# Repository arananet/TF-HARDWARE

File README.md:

# TF-HARDWARE
A backup (04-04-2017) of the last TF repo that includes the projects (TF520,TF530,A3640 & breakout). All the work belongs to Stephen Leary, I just share the files as a repo backup.

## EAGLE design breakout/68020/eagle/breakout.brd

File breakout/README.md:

Terrible Fire Break Out Boards
=================================

* 68020 - PGA114 Breakout

You may get any PCB manufacturer to produce the board for you. The board is 2-layer. I recommend these dirtypcbs links...

http://dirtypcbs.com/view.php?share=26129&accesskey=53f7f219ee0d339a3d1a7b1910aeaeed

* 68030 - PGA128 Breakout

You may get any PCB manufacturer to produce the board for you. The board is 2-layer. I recommend these dirtypcbs links...

http://dirtypcbs.com/view.php?share=28380&accesskey=9c851266aeee43fccca2846767b09b1c

* CD32 - MCA-182 Breakout

Work in Progress

* Libraries

The terriblefire.lbr file contains the following parts :-

XC9572XL-VQ64 (unverfied)

XC95144XL-TQ100 (unverified)

MC68SEC000-QFP64 (unverfied)

These parts are free to use but come with absolutely NO WARRANTY and in many cases have not been verified. 

* Tools

The following GPL tools are available.

54600.py - (Captures the output of a 56400 series scope and writes the output to a VCD file).

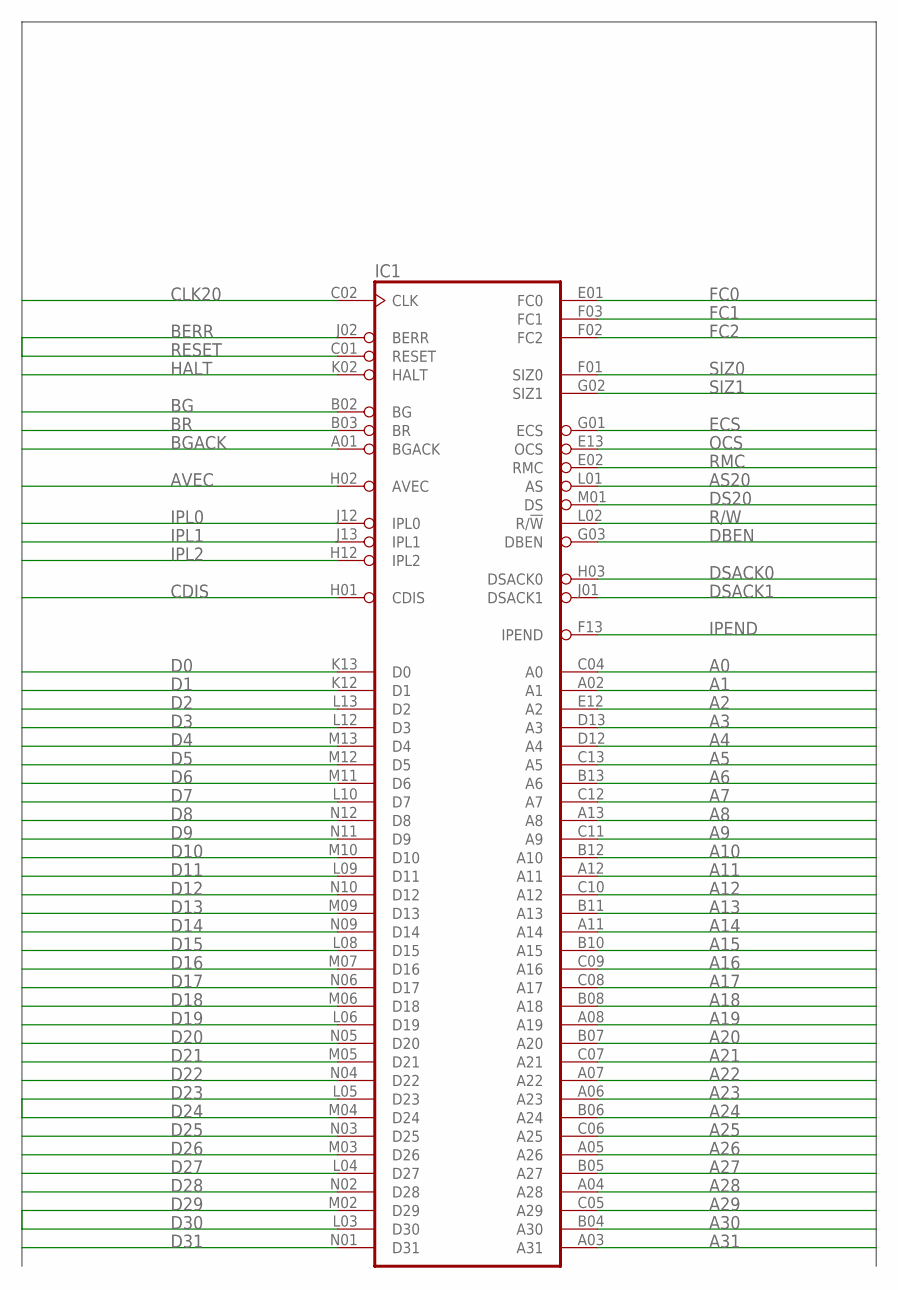
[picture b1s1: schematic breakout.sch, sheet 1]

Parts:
IC1: MC68020RC; MPGA114

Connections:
A0: IC1.C04 (A0); also elsewhere on the board
A1: IC1.A02 (A1); also elsewhere on the board
A2: IC1.E12 (A2); also elsewhere on the board
A3: IC1.D13 (A3); also elsewhere on the board
A4: IC1.D12 (A4); also elsewhere on the board
A5: IC1.C13 (A5); also elsewhere on the board
A6: IC1.B13 (A6); also elsewhere on the board
A7: IC1.C12 (A7); also elsewhere on the board
A8: IC1.A13 (A8); also elsewhere on the board
A9: IC1.C11 (A9); also elsewhere on the board
A10: IC1.B12 (A10); also elsewhere on the board
A11: IC1.A12 (A11); also elsewhere on the board
A12: IC1.C10 (A12); also elsewhere on the board
A13: IC1.B11 (A13); also elsewhere on the board
A14: IC1.A11 (A14); also elsewhere on the board
A15: IC1.B10 (A15); also elsewhere on the board
A16: IC1.C09 (A16); also elsewhere on the board
A17: IC1.C08 (A17); also elsewhere on the board
A18: IC1.B08 (A18); also elsewhere on the board
A19: IC1.A08 (A19); also elsewhere on the board
A20: IC1.B07 (A20); also elsewhere on the board
A21: IC1.C07 (A21); also elsewhere on the board
A22: IC1.A07 (A22); also elsewhere on the board
A23: IC1.A06 (A23); also elsewhere on the board
A24: IC1.B06 (A24); also elsewhere on the board
A25: IC1.C06 (A25); also elsewhere on the board
A26: IC1.A05 (A26); also elsewhere on the board
A27: IC1.B05 (A27); also elsewhere on the board
A28: IC1.A04 (A28); also elsewhere on the board
A29: IC1.C05 (A29); also elsewhere on the board
A30: IC1.B04 (A30); also elsewhere on the board
A31: IC1.A03 (A31); also elsewhere on the board
AS20: IC1.L01 (AS); also elsewhere on the board
AVEC: IC1.H02 (AVEC); also elsewhere on the board
BERR: IC1.J02 (BERR); also elsewhere on the board
BG: IC1.B02 (BG)
BGACK: IC1.A01 (BGACK); also elsewhere on the board
BR: IC1.B03 (BR); also elsewhere on the board
CDIS: IC1.H01 (CDIS); also elsewhere on the board
CLK20: IC1.C02 (CLK); also elsewhere on the board
D0: IC1.K13 (D0); also elsewhere on the board
D1: IC1.K12 (D1); also elsewhere on the board
D2: IC1.L13 (D2); also elsewhere on the board
D3: IC1.L12 (D3); also elsewhere on the board
D4: IC1.M13 (D4); also elsewhere on the board
D5: IC1.M12 (D5); also elsewhere on the board
D6: IC1.M11 (D6); also elsewhere on the board
D7: IC1.L10 (D7); also elsewhere on the board
D8: IC1.N12 (D8); also elsewhere on the board
D9: IC1.N11 (D9); also elsewhere on the board
D10: IC1.M10 (D10); also elsewhere on the board
D11: IC1.L09 (D11); also elsewhere on the board
D12: IC1.N10 (D12); also elsewhere on the board
D13: IC1.M09 (D13); also elsewhere on the board
D14: IC1.N09 (D14); also elsewhere on the board
D15: IC1.L08 (D15); also elsewhere on the board
D16: IC1.M07 (D16); also elsewhere on the board
D17: IC1.N06 (D17); also elsewhere on the board
D18: IC1.M06 (D18); also elsewhere on the board
D19: IC1.L06 (D19); also elsewhere on the board
D20: IC1.N05 (D20); also elsewhere on the board
D21: IC1.M05 (D21); also elsewhere on the board
D22: IC1.N04 (D22); also elsewhere on the board
D23: IC1.L05 (D23); also elsewhere on the board
D24: IC1.M04 (D24); also elsewhere on the board
D25: IC1.N03 (D25); also elsewhere on the board
D26: IC1.M03 (D26); also elsewhere on the board
D27: IC1.L04 (D27); also elsewhere on the board
D28: IC1.N02 (D28); also elsewhere on the board
D29: IC1.M02 (D29); also elsewhere on the board
D30: IC1.L03 (D30); also elsewhere on the board
D31: IC1.N01 (D31); also elsewhere on the board
DBEN: IC1.G03 (DBEN); also elsewhere on the board
DS20: IC1.M01 (DS); also elsewhere on the board
DSACK0: IC1.H03 (DSACK0); also elsewhere on the board
DSACK1: IC1.J01 (DSACK1); also elsewhere on the board
ECS: IC1.G01 (ECS); also elsewhere on the board
FC0: IC1.E01 (FC0); also elsewhere on the board
FC1: IC1.F03 (FC1); also elsewhere on the board
FC2: IC1.F02 (FC2); also elsewhere on the board
GND: IC1.A10 (GND), IC1.B01 (GND), IC1.B09 (GND), IC1.C03 (GND), IC1.F12 (GND), IC1.G12 (GND), IC1.H13 (GND), IC1.J03 (GND), IC1.K01 (GND), IC1.K03 (GND), IC1.L07 (GND), IC1.L11 (GND), IC1.N07 (GND); also elsewhere on the board
HALT: IC1.K02 (HALT); also elsewhere on the board
IPEND: IC1.F13 (IPEND); also elsewhere on the board
IPL0: IC1.J12 (IPL0); also elsewhere on the board
IPL1: IC1.J13 (IPL1); also elsewhere on the board
IPL2: IC1.H12 (IPL2); also elsewhere on the board
OCS: IC1.E13 (OCS); also elsewhere on the board
R/W: IC1.L02 (R/!W); also elsewhere on the board
RESET: IC1.C01 (RESET); also elsewhere on the board
RMC: IC1.E02 (RMC); also elsewhere on the board
SIZ0: IC1.F01 (SIZ0); also elsewhere on the board
SIZ1: IC1.G02 (SIZ1); also elsewhere on the board
VCC: IC1.A09 (VCC), IC1.D01 (VCC), IC1.D02 (VCC), IC1.D03 (VCC), IC1.E03 (VCC), IC1.G11 (VCC), IC1.G13 (VCC), IC1.M08 (VCC), IC1.N08 (VCC), IC1.N13 (VCC); also elsewhere on the board

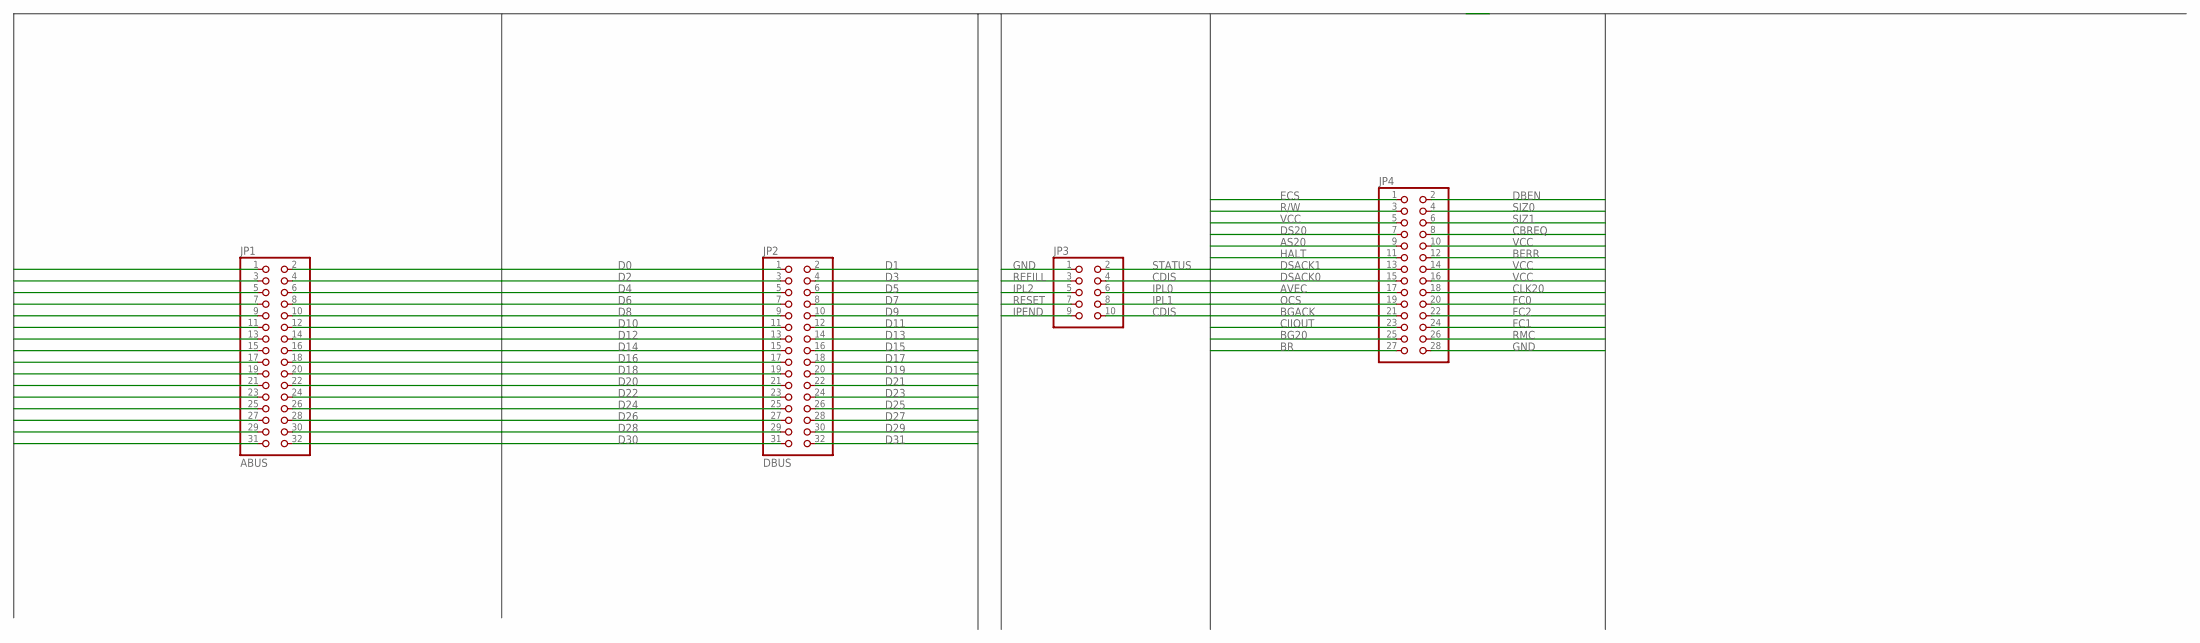
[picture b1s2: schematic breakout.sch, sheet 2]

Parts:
JP1: ABUS; 2X16
JP2: DBUS; 2X16
JP3: PINHD-2X5; 2X05
JP4: PINHD-2X14; 2X14

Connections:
A0: JP1.1; also elsewhere on the board
A1: JP1.2; also elsewhere on the board
A2: JP1.3; also elsewhere on the board
A3: JP1.4; also elsewhere on the board
A4: JP1.5; also elsewhere on the board
A5: JP1.6; also elsewhere on the board
A6: JP1.7; also elsewhere on the board
A7: JP1.8; also elsewhere on the board
A8: JP1.9; also elsewhere on the board
A9: JP1.10; also elsewhere on the board
A10: JP1.11; also elsewhere on the board
A11: JP1.12; also elsewhere on the board
A12: JP1.13; also elsewhere on the board
A13: JP1.14; also elsewhere on the board
A14: JP1.15; also elsewhere on the board
A15: JP1.16; also elsewhere on the board
A16: JP1.17; also elsewhere on the board
A17: JP1.18; also elsewhere on the board
A18: JP1.19; also elsewhere on the board
A19: JP1.20; also elsewhere on the board
A20: JP1.21; also elsewhere on the board
A21: JP1.22; also elsewhere on the board
A22: JP1.23; also elsewhere on the board
A23: JP1.24; also elsewhere on the board
A24: JP1.25; also elsewhere on the board
A25: JP1.26; also elsewhere on the board
A26: JP1.27; also elsewhere on the board
A27: JP1.28; also elsewhere on the board
A28: JP1.29; also elsewhere on the board
A29: JP1.30; also elsewhere on the board
A30: JP1.31; also elsewhere on the board
A31: JP1.32; also elsewhere on the board
AS20: JP4.9; also elsewhere on the board
AVEC: JP4.17; also elsewhere on the board
BERR: JP4.12; also elsewhere on the board
BG20: JP4.25
BGACK: JP4.21; also elsewhere on the board
BR: JP4.27; also elsewhere on the board
CBREQ: JP4.8
CDIS: JP3.4, JP3.10; also elsewhere on the board
CIIOUT: JP4.23
CLK20: JP4.18; also elsewhere on the board
D0: JP2.1; also elsewhere on the board
D1: JP2.2; also elsewhere on the board
D2: JP2.3; also elsewhere on the board
D3: JP2.4; also elsewhere on the board
D4: JP2.5; also elsewhere on the board
D5: JP2.6; also elsewhere on the board
D6: JP2.7; also elsewhere on the board
D7: JP2.8; also elsewhere on the board
D8: JP2.9; also elsewhere on the board
D9: JP2.10; also elsewhere on the board
D10: JP2.11; also elsewhere on the board
D11: JP2.12; also elsewhere on the board
D12: JP2.13; also elsewhere on the board
D13: JP2.14; also elsewhere on the board
D14: JP2.15; also elsewhere on the board
D15: JP2.16; also elsewhere on the board
D16: JP2.17; also elsewhere on the board
D17: JP2.18; also elsewhere on the board
D18: JP2.19; also elsewhere on the board
D19: JP2.20; also elsewhere on the board
D20: JP2.21; also elsewhere on the board
D21: JP2.22; also elsewhere on the board
D22: JP2.23; also elsewhere on the board
D23: JP2.24; also elsewhere on the board
D24: JP2.25; also elsewhere on the board
D25: JP2.26; also elsewhere on the board
D26: JP2.27; also elsewhere on the board
D27: JP2.28; also elsewhere on the board
D28: JP2.29; also elsewhere on the board
D29: JP2.30; also elsewhere on the board
D30: JP2.31; also elsewhere on the board
D31: JP2.32; also elsewhere on the board
DBEN: JP4.2; also elsewhere on the board
DS20: JP4.7; also elsewhere on the board
DSACK0: JP4.15; also elsewhere on the board
DSACK1: JP4.13; also elsewhere on the board
ECS: JP4.1; also elsewhere on the board
FC0: JP4.20; also elsewhere on the board
FC1: JP4.24; also elsewhere on the board
FC2: JP4.22; also elsewhere on the board
GND: JP3.1, JP4.28; also elsewhere on the board
HALT: JP4.11; also elsewhere on the board
IPEND: JP3.9; also elsewhere on the board
IPL0: JP3.6; also elsewhere on the board
IPL1: JP3.8; also elsewhere on the board
IPL2: JP3.5; also elsewhere on the board
OCS: JP4.19; also elsewhere on the board
R/W: JP4.3; also elsewhere on the board
REFILL: JP3.3
RESET: JP3.7; also elsewhere on the board
RMC: JP4.26; also elsewhere on the board
SIZ0: JP4.4; also elsewhere on the board
SIZ1: JP4.6; also elsewhere on the board
STATUS: JP3.2
VCC: JP4.5, JP4.10, JP4.14, JP4.16; also elsewhere on the board

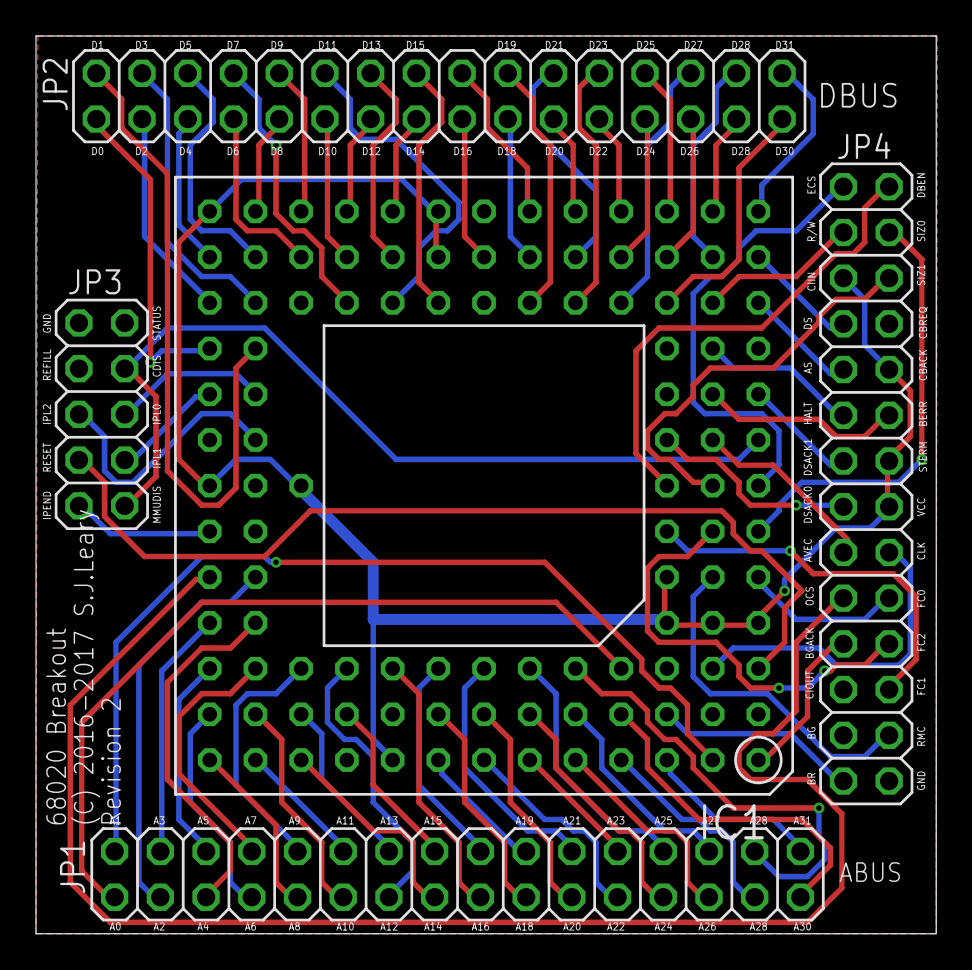
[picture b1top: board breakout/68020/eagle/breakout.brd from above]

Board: 2 copper layers, 50.0 x 49.9 mm, 5 parts (0 on the bottom side), 92 nets.

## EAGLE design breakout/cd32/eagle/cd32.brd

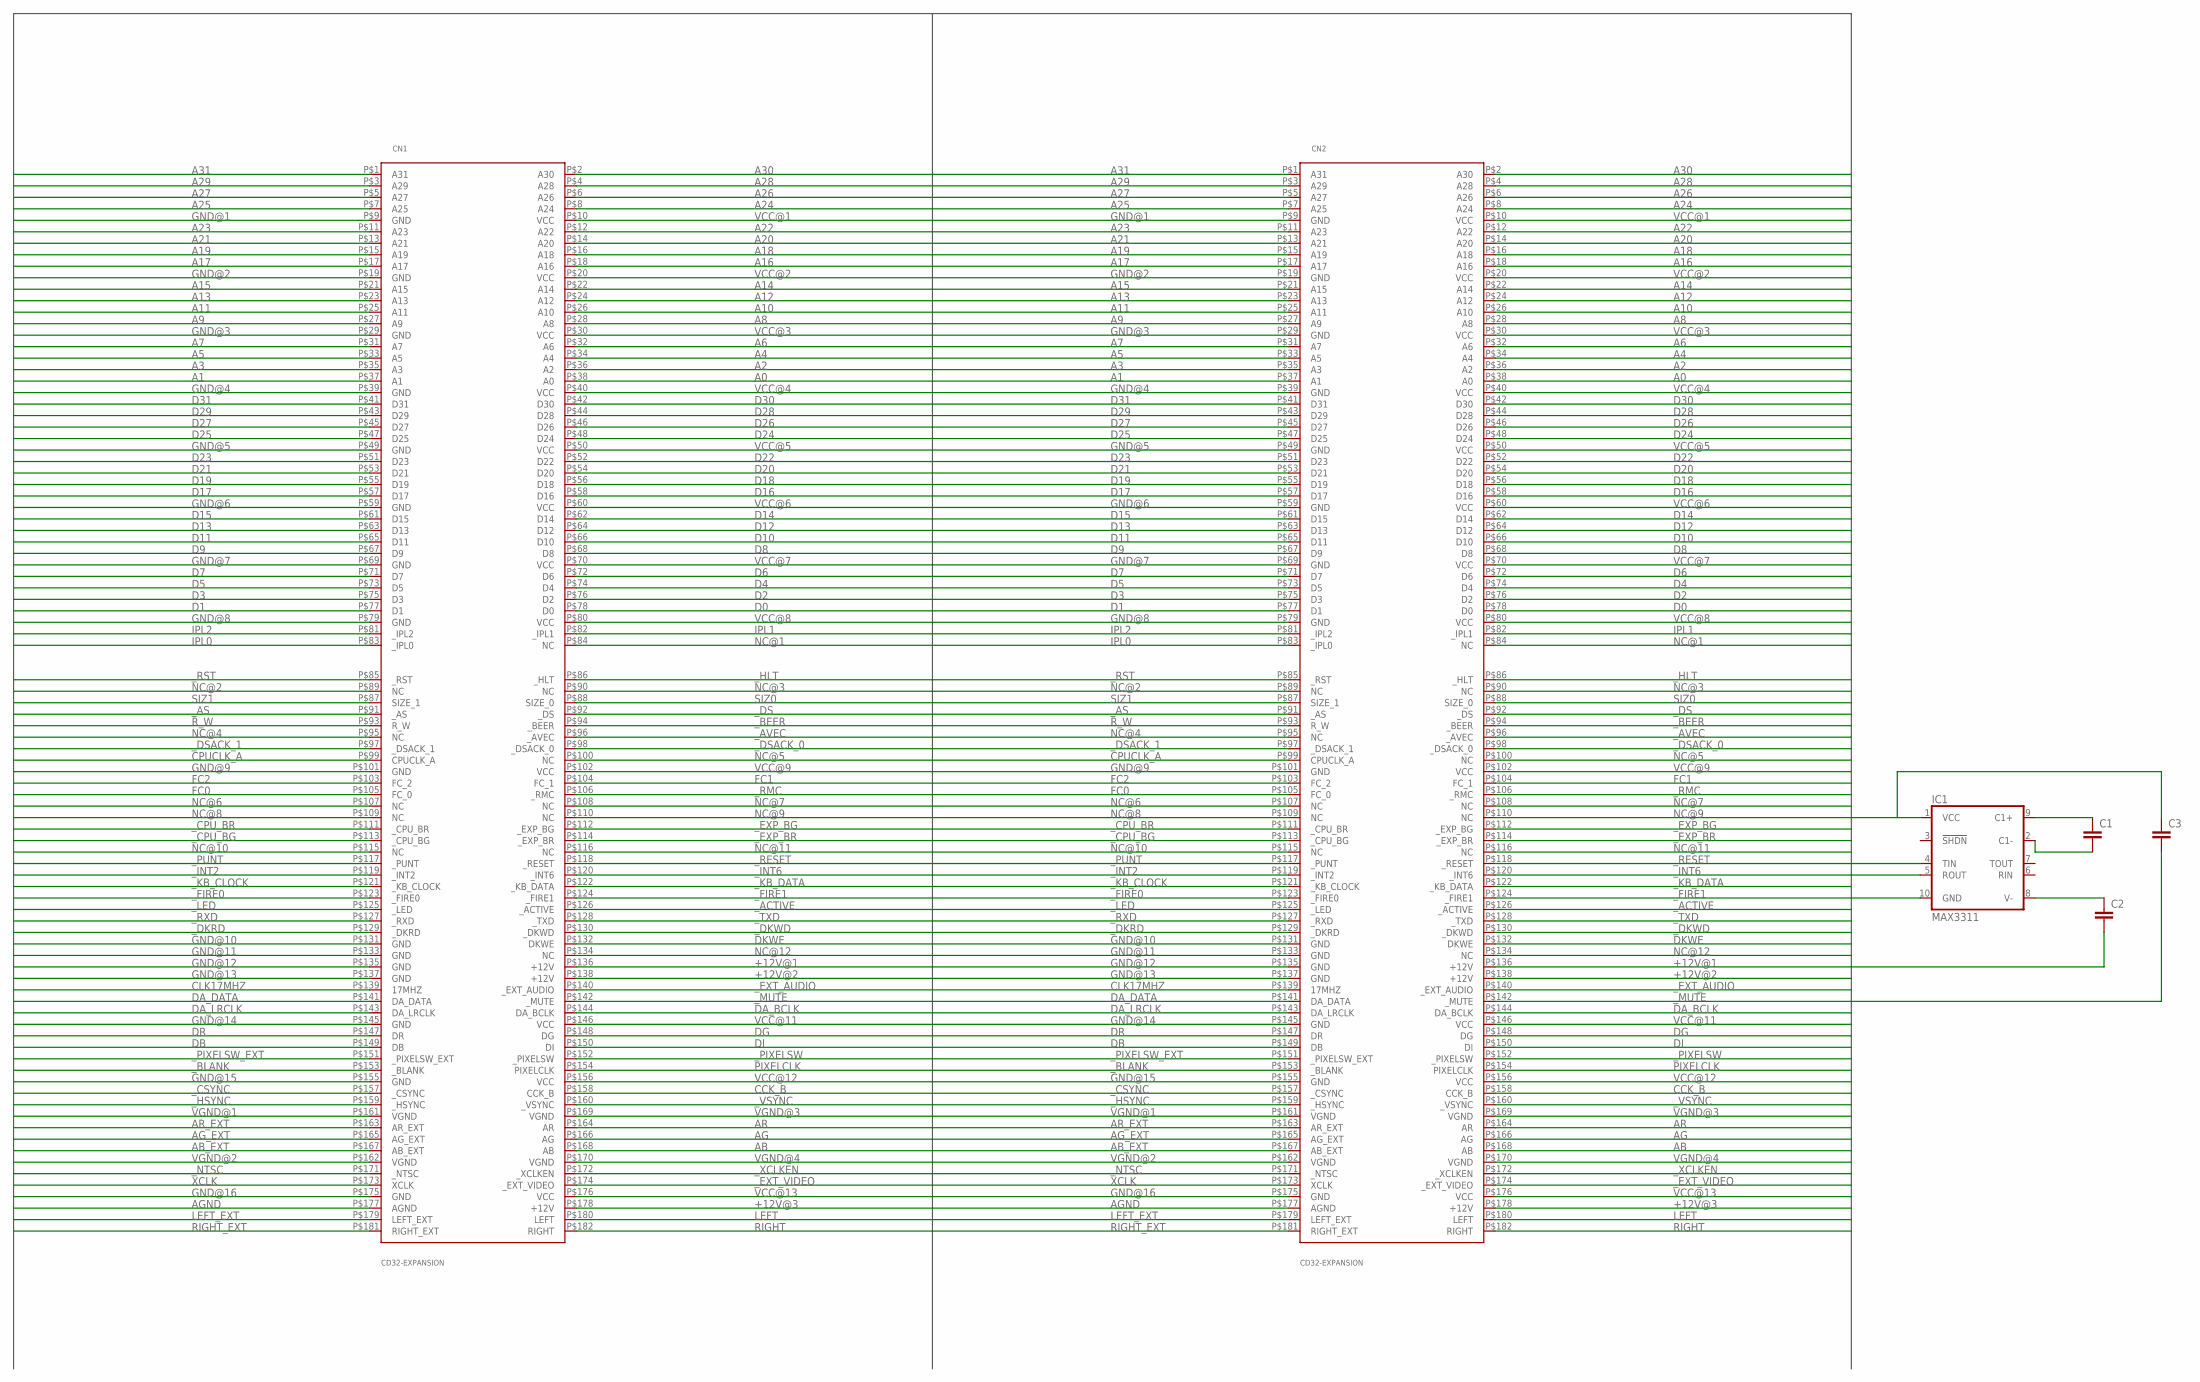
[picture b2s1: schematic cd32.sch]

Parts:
C1, C2, C3: CC1206; C1206
CN1, CN2: CD32-EXPANSION; CD32_EXPANSION_182_MCA
IC1: MAX3311; UMAX10

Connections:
+12V@1: C2.2, CN1.P$136 (+12V), CN2.P$136 (+12V)
+12V@2: CN1.P$138 (+12V), CN2.P$138 (+12V)
+12V@3: CN1.P$178 (+12V), CN2.P$178 (+12V)
A0: CN1.P$38 (A0), CN2.P$38 (A0)
A1: CN1.P$37 (A1), CN2.P$37 (A1)
A2: CN1.P$36 (A2), CN2.P$36 (A2)
A3: CN1.P$35 (A3), CN2.P$35 (A3)
A4: CN1.P$34 (A4), CN2.P$34 (A4)
A5: CN1.P$33 (A5), CN2.P$33 (A5)
A6: CN1.P$32 (A6), CN2.P$32 (A6)
A7: CN1.P$31 (A7), CN2.P$31 (A7)
A8: CN1.P$28 (A8), CN2.P$28 (A8)
A9: CN1.P$27 (A9), CN2.P$27 (A9)
A10: CN1.P$26 (A10), CN2.P$26 (A10)
A11: CN1.P$25 (A11), CN2.P$25 (A11)
A12: CN1.P$24 (A12), CN2.P$24 (A12)
A13: CN1.P$23 (A13), CN2.P$23 (A13)
A14: CN1.P$22 (A14), CN2.P$22 (A14)
A15: CN1.P$21 (A15), CN2.P$21 (A15)
A16: CN1.P$18 (A16), CN2.P$18 (A16)
A17: CN1.P$17 (A17), CN2.P$17 (A17)
A18: CN1.P$16 (A18), CN2.P$16 (A18)
A19: CN1.P$15 (A19), CN2.P$15 (A19)
A20: CN1.P$14 (A20), CN2.P$14 (A20)
A21: CN1.P$13 (A21), CN2.P$13 (A21)
A22: CN1.P$12 (A22), CN2.P$12 (A22)
A23: CN1.P$11 (A23), CN2.P$11 (A23)
A24: CN1.P$8 (A24), CN2.P$8 (A24)
A25: CN1.P$7 (A25), CN2.P$7 (A25)
A26: CN1.P$6 (A26), CN2.P$6 (A26)
A27: CN1.P$5 (A27), CN2.P$5 (A27)
A28: CN1.P$4 (A28), CN2.P$4 (A28)
A29: CN1.P$3 (A29), CN2.P$3 (A29)
A30: CN1.P$2 (A30), CN2.P$2 (A30)
A31: CN1.P$1 (A31), CN2.P$1 (A31)
AB: CN1.P$168 (AB), CN2.P$168 (AB)
AB_EXT: CN1.P$167 (AB_EXT), CN2.P$167 (AB_EXT)
AG: CN1.P$166 (AG), CN2.P$166 (AG)
AGND: CN1.P$177 (AGND), CN2.P$177 (AGND)
AG_EXT: CN1.P$165 (AG_EXT), CN2.P$165 (AG_EXT)
AR: CN1.P$164 (AR), CN2.P$164 (AR)
AR_EXT: CN1.P$163 (AR_EXT), CN2.P$163 (AR_EXT)
CCK_B: CN1.P$158 (CCK_B), CN2.P$158 (CCK_B)
CLK17MHZ: CN1.P$139 (17MHZ), CN2.P$139 (17MHZ)
CPUCLK_A: CN1.P$99 (CPUCLK_A), CN2.P$99 (CPUCLK_A)
D0: CN1.P$78 (D0), CN2.P$78 (D0)
D1: CN1.P$77 (D1), CN2.P$77 (D1)
D2: CN1.P$76 (D2), CN2.P$76 (D2)
D3: CN1.P$75 (D3), CN2.P$75 (D3)
D4: CN1.P$74 (D4), CN2.P$74 (D4)
D5: CN1.P$73 (D5), CN2.P$73 (D5)
D6: CN1.P$72 (D6), CN2.P$72 (D6)
D7: CN1.P$71 (D7), CN2.P$71 (D7)
D8: CN1.P$68 (D8), CN2.P$68 (D8)
D9: CN1.P$67 (D9), CN2.P$67 (D9)
D10: CN1.P$66 (D10), CN2.P$66 (D10)
D11: CN1.P$65 (D11), CN2.P$65 (D11)
D12: CN1.P$64 (D12), CN2.P$64 (D12)
D13: CN1.P$63 (D13), CN2.P$63 (D13)
D14: CN1.P$62 (D14), CN2.P$62 (D14)
D15: CN1.P$61 (D15), CN2.P$61 (D15)
D16: CN1.P$58 (D16), CN2.P$58 (D16)
D17: CN1.P$57 (D17), CN2.P$57 (D17)
D18: CN1.P$56 (D18), CN2.P$56 (D18)
D19: CN1.P$55 (D19), CN2.P$55 (D19)
D20: CN1.P$54 (D20), CN2.P$54 (D20)
D21: CN1.P$53 (D21), CN2.P$53 (D21)
D22: CN1.P$52 (D22), CN2.P$52 (D22)
D23: CN1.P$51 (D23), CN2.P$51 (D23)
D24: CN1.P$48 (D24), CN2.P$48 (D24)
D25: CN1.P$47 (D25), CN2.P$47 (D25)
D26: CN1.P$46 (D26), CN2.P$46 (D26)
D27: CN1.P$45 (D27), CN2.P$45 (D27)
D28: CN1.P$44 (D28), CN2.P$44 (D28)
D29: CN1.P$43 (D29), CN2.P$43 (D29)
D30: CN1.P$42 (D30), CN2.P$42 (D30)
D31: CN1.P$41 (D31), CN2.P$41 (D31)
DA_BCLK: CN1.P$144 (DA_BCLK), CN2.P$144 (DA_BCLK)
DA_DATA: CN1.P$141 (DA_DATA), CN2.P$141 (DA_DATA)
DA_LRCLK: CN1.P$143 (DA_LRCLK), CN2.P$143 (DA_LRCLK)
DB: CN1.P$149 (DB), CN2.P$149 (DB)
DG: CN1.P$148 (DG), CN2.P$148 (DG)
DI: CN1.P$150 (DI), CN2.P$150 (DI)
DKWE: CN1.P$132 (DKWE), CN2.P$132 (DKWE)
DR: CN1.P$147 (DR), CN2.P$147 (DR)
FC0: CN1.P$105 (FC_0), CN2.P$105 (FC_0)
FC1: CN1.P$104 (FC_1), CN2.P$104 (FC_1)
FC2: CN1.P$103 (FC_2), CN2.P$103 (FC_2)
GND: C3.2, IC1.10 (GND)
GND@1: CN1.P$9 (GND), CN2.P$9 (GND)
GND@2: CN1.P$19 (GND), CN2.P$19 (GND)
GND@3: CN1.P$29 (GND), CN2.P$29 (GND)
GND@4: CN1.P$39 (GND), CN2.P$39 (GND)
GND@5: CN1.P$49 (GND), CN2.P$49 (GND)
GND@6: CN1.P$59 (GND), CN2.P$59 (GND)
GND@7: CN1.P$69 (GND), CN2.P$69 (GND)
GND@8: CN1.P$79 (GND), CN2.P$79 (GND)
GND@9: CN1.P$101 (GND), CN2.P$101 (GND)
GND@10: CN1.P$131 (GND), CN2.P$131 (GND)
GND@11: CN1.P$133 (GND), CN2.P$133 (GND)
GND@12: CN1.P$135 (GND), CN2.P$135 (GND)
GND@13: CN1.P$137 (GND), CN2.P$137 (GND)
GND@14: CN1.P$145 (GND), CN2.P$145 (GND)
GND@15: CN1.P$155 (GND), CN2.P$155 (GND)
GND@16: CN1.P$175 (GND), CN2.P$175 (GND)
IPL0: CN1.P$83 (_IPL0), CN2.P$83 (_IPL0)
IPL1: CN1.P$82 (_IPL1), CN2.P$82 (_IPL1)
IPL2: CN1.P$81 (_IPL2), CN2.P$81 (_IPL2)
LEFT: CN1.P$180 (LEFT), CN2.P$180 (LEFT)
LEFT_EXT: CN1.P$179 (LEFT_EXT), CN2.P$179 (LEFT_EXT)
unnamed: C1.1, IC1.9 (C1+)
unnamed: C1.2, IC1.2 (C1-)
unnamed: C2.1, IC1.8 (V-)
NC@1: CN1.P$84 (NC), CN2.P$84 (NC)
NC@2: CN1.P$89 (NC), CN2.P$89 (NC)
NC@3: CN1.P$90 (NC), CN2.P$90 (NC)
NC@4: CN1.P$95 (NC), CN2.P$95 (NC)
NC@5: CN1.P$100 (NC), CN2.P$100 (NC)
NC@6: CN1.P$107 (NC), CN2.P$107 (NC)
NC@7: CN1.P$108 (NC), CN2.P$108 (NC)
NC@8: CN1.P$109 (NC), CN2.P$109 (NC)
NC@9: CN1.P$110 (NC), CN2.P$110 (NC)
NC@10: CN1.P$115 (NC), CN2.P$115 (NC)
NC@11: CN1.P$116 (NC), CN2.P$116 (NC)
NC@12: CN1.P$134 (NC), CN2.P$134 (NC)
PIXELCLK: CN1.P$154 (PIXELCLK), CN2.P$154 (PIXELCLK)
RIGHT: CN1.P$182 (RIGHT), CN2.P$182 (RIGHT)
RIGHT_EXT: CN1.P$181 (RIGHT_EXT), CN2.P$181 (RIGHT_EXT)
R_W: CN1.P$93 (R_W), CN2.P$93 (R_W)
SIZ0: CN1.P$88 (SIZE_0), CN2.P$88 (SIZE_0)
SIZ1: CN1.P$87 (SIZE_1), CN2.P$87 (SIZE_1)
VCC: C3.1, IC1.1 (VCC)
VCC@1: CN1.P$10 (VCC), CN2.P$10 (VCC)
VCC@2: CN1.P$20 (VCC), CN2.P$20 (VCC)
VCC@3: CN1.P$30 (VCC), CN2.P$30 (VCC)
VCC@4: CN1.P$40 (VCC), CN2.P$40 (VCC)
VCC@5: CN1.P$50 (VCC), CN2.P$50 (VCC)
VCC@6: CN1.P$60 (VCC), CN2.P$60 (VCC)
VCC@7: CN1.P$70 (VCC), CN2.P$70 (VCC)
VCC@8: CN1.P$80 (VCC), CN2.P$80 (VCC)
VCC@9: CN1.P$102 (VCC), CN2.P$102 (VCC)
VCC@11: CN1.P$146 (VCC), CN2.P$146 (VCC)
VCC@12: CN1.P$156 (VCC), CN2.P$156 (VCC)
VCC@13: CN1.P$176 (VCC), CN2.P$176 (VCC)
VGND@1: CN1.P$161 (VGND), CN2.P$161 (VGND)
VGND@2: CN1.P$162 (VGND), CN2.P$162 (VGND)
VGND@3: CN1.P$169 (VGND), CN2.P$169 (VGND)
VGND@4: CN1.P$170 (VGND), CN2.P$170 (VGND)
XCLK: CN1.P$173 (XCLK), CN2.P$173 (XCLK)
_ACTIVE: CN1.P$126 (_ACTIVE), CN2.P$126 (_ACTIVE)
_AS: CN1.P$91 (_AS), CN2.P$91 (_AS)
_AVEC: CN1.P$96 (_AVEC), CN2.P$96 (_AVEC)
_BEER: CN1.P$94 (_BEER), CN2.P$94 (_BEER)
_BLANK: CN1.P$153 (_BLANK), CN2.P$153 (_BLANK)
_CPU_BG: CN1.P$113 (_CPU_BG), CN2.P$113 (_CPU_BG)
_CPU_BR: CN1.P$111 (_CPU_BR), CN2.P$111 (_CPU_BR)
_CSYNC: CN1.P$157 (_CSYNC), CN2.P$157 (_CSYNC)
_DKRD: CN1.P$129 (_DKRD), CN2.P$129 (_DKRD)
_DKWD: CN1.P$130 (_DKWD), CN2.P$130 (_DKWD)
_DS: CN1.P$92 (_DS), CN2.P$92 (_DS)
_DSACK_0: CN1.P$98 (_DSACK_0), CN2.P$98 (_DSACK_0)
_DSACK_1: CN1.P$97 (_DSACK_1), CN2.P$97 (_DSACK_1)
_EXP_BG: CN1.P$112 (_EXP_BG), CN2.P$112 (_EXP_BG)
_EXP_BR: CN1.P$114 (_EXP_BR), CN2.P$114 (_EXP_BR)
_EXT_AUDIO: CN1.P$140 (_EXT_AUDIO), CN2.P$140 (_EXT_AUDIO)
_EXT_VIDEO: CN1.P$174 (_EXT_VIDEO), CN2.P$174 (_EXT_VIDEO)
_FIRE0: CN1.P$123 (_FIRE0), CN2.P$123 (_FIRE0)
_FIRE1: CN1.P$124 (_FIRE1), CN2.P$124 (_FIRE1)
_HLT: CN1.P$86 (_HLT), CN2.P$86 (_HLT)
_HSYNC: CN1.P$159 (_HSYNC), CN2.P$159 (_HSYNC)
_INT2: CN1.P$119 (_INT2), CN2.P$119 (_INT2)
_INT6: CN1.P$120 (_INT6), CN2.P$120 (_INT6)
_KB_CLOCK: CN1.P$121 (_KB_CLOCK), CN2.P$121 (_KB_CLOCK)
_KB_DATA: CN1.P$122 (_KB_DATA), CN2.P$122 (_KB_DATA)
_LED: CN1.P$125 (_LED), CN2.P$125 (_LED)
_MUTE: CN1.P$142 (_MUTE), CN2.P$142 (_MUTE)
_NTSC: CN1.P$171 (_NTSC), CN2.P$171 (_NTSC)
_PIXELSW: CN1.P$152 (_PIXELSW), CN2.P$152 (_PIXELSW)
_PIXELSW_EXT: CN1.P$151 (_PIXELSW_EXT), CN2.P$151 (_PIXELSW_EXT)
_PUNT: CN1.P$117 (_PUNT), CN2.P$117 (_PUNT)
_RESET: CN1.P$118 (_RESET), CN2.P$118 (_RESET)
_RMC: CN1.P$106 (_RMC), CN2.P$106 (_RMC)
_RST: CN1.P$85 (_RST), CN2.P$85 (_RST)
_RXD: CN1.P$127 (_RXD), CN2.P$127 (_RXD), IC1.5 (ROUT)
_TXD: CN1.P$128 (_TXD), CN2.P$128 (_TXD), IC1.4 (TIN)
_VSYNC: CN1.P$160 (_VSYNC), CN2.P$160 (_VSYNC)
_XCLKEN: CN1.P$172 (_XCLKEN), CN2.P$172 (_XCLKEN)

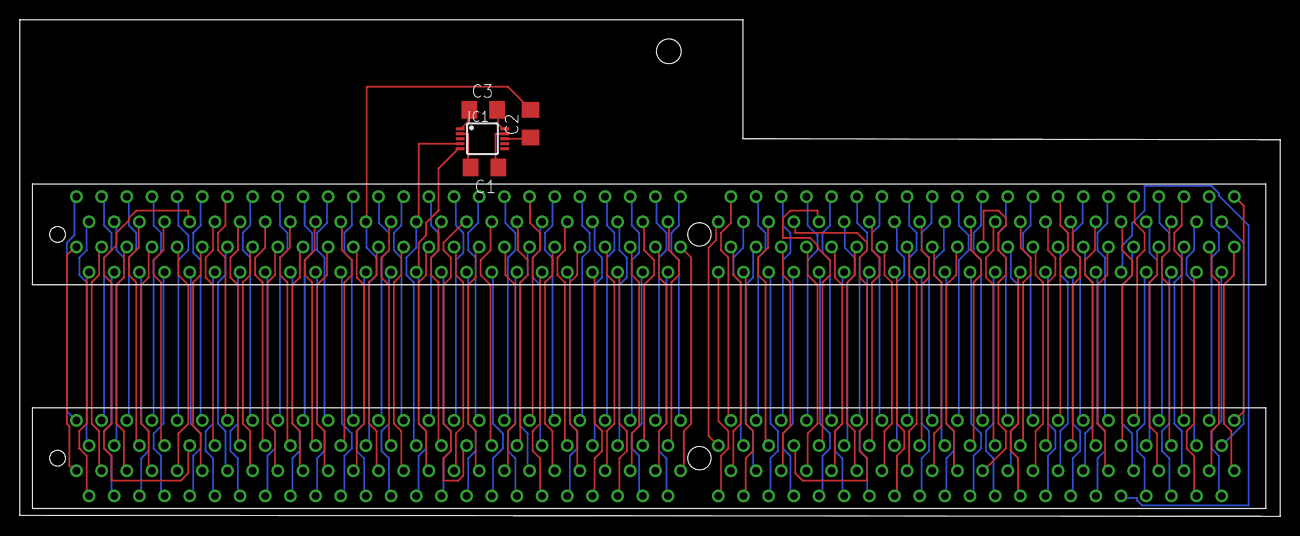
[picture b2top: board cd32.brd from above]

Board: 2 copper layers, 127.2 x 50.1 mm, 6 parts (0 on the bottom side), 187 nets.

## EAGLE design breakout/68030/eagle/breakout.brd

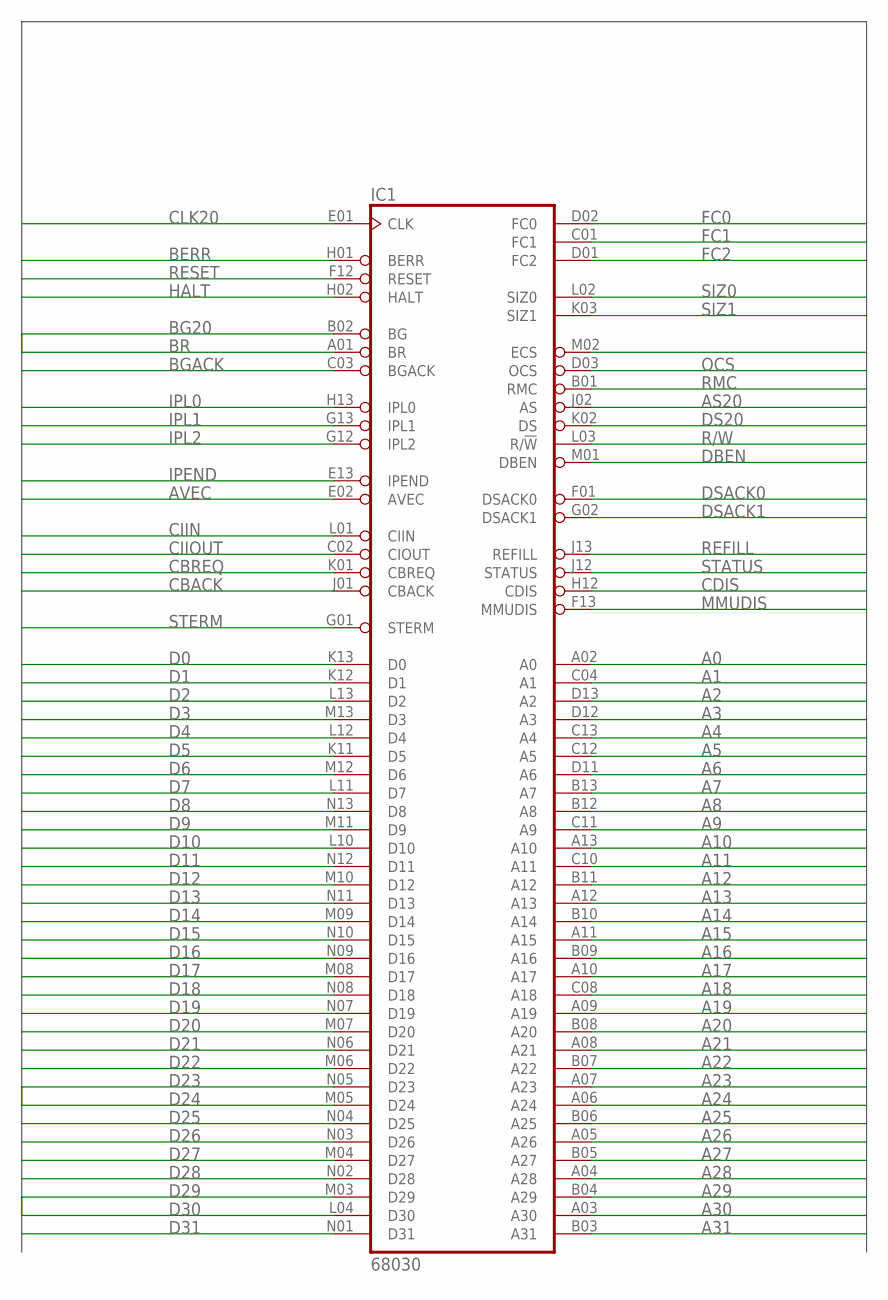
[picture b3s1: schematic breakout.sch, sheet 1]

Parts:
IC1: 68030; MPGA128

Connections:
A0: IC1.A02 (A0); also elsewhere on the board
A1: IC1.C04 (A1); also elsewhere on the board
A2: IC1.D13 (A2); also elsewhere on the board
A3: IC1.D12 (A3); also elsewhere on the board
A4: IC1.C13 (A4); also elsewhere on the board
A5: IC1.C12 (A5); also elsewhere on the board
A6: IC1.D11 (A6); also elsewhere on the board
A7: IC1.B13 (A7); also elsewhere on the board
A8: IC1.B12 (A8); also elsewhere on the board
A9: IC1.C11 (A9); also elsewhere on the board
A10: IC1.A13 (A10); also elsewhere on the board
A11: IC1.C10 (A11); also elsewhere on the board
A12: IC1.B11 (A12); also elsewhere on the board
A13: IC1.A12 (A13); also elsewhere on the board
A14: IC1.B10 (A14); also elsewhere on the board
A15: IC1.A11 (A15); also elsewhere on the board
A16: IC1.B09 (A16); also elsewhere on the board
A17: IC1.A10 (A17); also elsewhere on the board
A18: IC1.C08 (A18); also elsewhere on the board
A19: IC1.A09 (A19); also elsewhere on the board
A20: IC1.B08 (A20); also elsewhere on the board
A21: IC1.A08 (A21); also elsewhere on the board
A22: IC1.B07 (A22); also elsewhere on the board
A23: IC1.A07 (A23); also elsewhere on the board
A24: IC1.A06 (A24); also elsewhere on the board
A25: IC1.B06 (A25); also elsewhere on the board
A26: IC1.A05 (A26); also elsewhere on the board
A27: IC1.B05 (A27); also elsewhere on the board
A28: IC1.A04 (A28); also elsewhere on the board
A29: IC1.B04 (A29); also elsewhere on the board
A30: IC1.A03 (A30); also elsewhere on the board
A31: IC1.B03 (A31); also elsewhere on the board
AS20: IC1.J02 (AS); also elsewhere on the board
AVEC: IC1.E02 (AVEC); also elsewhere on the board
BERR: IC1.H01 (BERR); also elsewhere on the board
BG20: IC1.B02 (BG); also elsewhere on the board
BGACK: IC1.C03 (BGACK); also elsewhere on the board
BR: IC1.A01 (BR); also elsewhere on the board
CBACK: IC1.J01 (CBACK); also elsewhere on the board
CBREQ: IC1.K01 (CBREQ); also elsewhere on the board
CDIS: IC1.H12 (CDIS); also elsewhere on the board
CIIN: IC1.L01 (CIIN); also elsewhere on the board
CIIOUT: IC1.C02 (CIOUT); also elsewhere on the board
CLK20: IC1.E01 (CLK); also elsewhere on the board
D0: IC1.K13 (D0); also elsewhere on the board
D1: IC1.K12 (D1); also elsewhere on the board
D2: IC1.L13 (D2); also elsewhere on the board
D3: IC1.M13 (D3); also elsewhere on the board
D4: IC1.L12 (D4); also elsewhere on the board
D5: IC1.K11 (D5); also elsewhere on the board
D6: IC1.M12 (D6); also elsewhere on the board
D7: IC1.L11 (D7); also elsewhere on the board
D8: IC1.N13 (D8); also elsewhere on the board
D9: IC1.M11 (D9); also elsewhere on the board
D10: IC1.L10 (D10); also elsewhere on the board
D11: IC1.N12 (D11); also elsewhere on the board
D12: IC1.M10 (D12); also elsewhere on the board
D13: IC1.N11 (D13); also elsewhere on the board
D14: IC1.M09 (D14); also elsewhere on the board
D15: IC1.N10 (D15); also elsewhere on the board
D16: IC1.N09 (D16); also elsewhere on the board
D17: IC1.M08 (D17); also elsewhere on the board
D18: IC1.N08 (D18); also elsewhere on the board
D19: IC1.N07 (D19); also elsewhere on the board
D20: IC1.M07 (D20); also elsewhere on the board
D21: IC1.N06 (D21); also elsewhere on the board
D22: IC1.M06 (D22); also elsewhere on the board
D23: IC1.N05 (D23); also elsewhere on the board
D24: IC1.M05 (D24); also elsewhere on the board
D25: IC1.N04 (D25); also elsewhere on the board
D26: IC1.N03 (D26); also elsewhere on the board
D27: IC1.M04 (D27); also elsewhere on the board
D28: IC1.N02 (D28); also elsewhere on the board
D29: IC1.M03 (D29); also elsewhere on the board
D30: IC1.L04 (D30); also elsewhere on the board
D31: IC1.N01 (D31); also elsewhere on the board
DBEN: IC1.M01 (DBEN); also elsewhere on the board
DS20: IC1.K02 (DS); also elsewhere on the board
DSACK0: IC1.F01 (DSACK0); also elsewhere on the board
DSACK1: IC1.G02 (DSACK1); also elsewhere on the board
ECS: IC1.M02 (ECS); also elsewhere on the board
FC0: IC1.D02 (FC0); also elsewhere on the board
FC1: IC1.C01 (FC1); also elsewhere on the board
FC2: IC1.D01 (FC2); also elsewhere on the board
GND: IC1.C05 (GND), IC1.C07 (GND), IC1.C09 (GND), IC1.E03 (GND), IC1.E11 (GND), IC1.F03 (GND), IC1.G03 (GND), IC1.G11 (GND), IC1.J03 (GND), IC1.J11 (GND), IC1.L05 (GND), IC1.L07 (GND), IC1.L08 (GND), IC1.L09 (GND); also elsewhere on the board
HALT: IC1.H02 (HALT); also elsewhere on the board
IPEND: IC1.E13 (IPEND); also elsewhere on the board
IPL0: IC1.H13 (IPL0); also elsewhere on the board
IPL1: IC1.G13 (IPL1); also elsewhere on the board
IPL2: IC1.G12 (IPL2); also elsewhere on the board
MMUDIS: IC1.F13 (MMUDIS); also elsewhere on the board
OCS: IC1.D03 (OCS); also elsewhere on the board
R/W: IC1.L03 (R/!W); also elsewhere on the board
REFILL: IC1.J13 (REFILL); also elsewhere on the board
RESET: IC1.F12 (RESET); also elsewhere on the board
RMC: IC1.B01 (RMC); also elsewhere on the board
SIZ0: IC1.L02 (SIZ0); also elsewhere on the board
SIZ1: IC1.K03 (SIZ1); also elsewhere on the board
STATUS: IC1.J12 (STATUS); also elsewhere on the board
STERM: IC1.G01 (STERM); also elsewhere on the board
VCC: IC1.C06 (VCC), IC1.D04 (VCC), IC1.D10 (VCC), IC1.F02 (VCC), IC1.F11 (VCC), IC1.H03 (VCC), IC1.H11 (VCC), IC1.K04 (VCC), IC1.K10 (VCC), IC1.L06 (VCC); also elsewhere on the board

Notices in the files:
breakout/68020/eagle/breakout.brd:
(C) 2016-2017 S.J.Leary
breakout/68030/eagle/breakout.brd:
(C) 2016 S.J.Leary
breakout/cd32/eagle/cd32.brd:
(C) 2017 S.J Leary
Publushed Under the GNU GPLv2
